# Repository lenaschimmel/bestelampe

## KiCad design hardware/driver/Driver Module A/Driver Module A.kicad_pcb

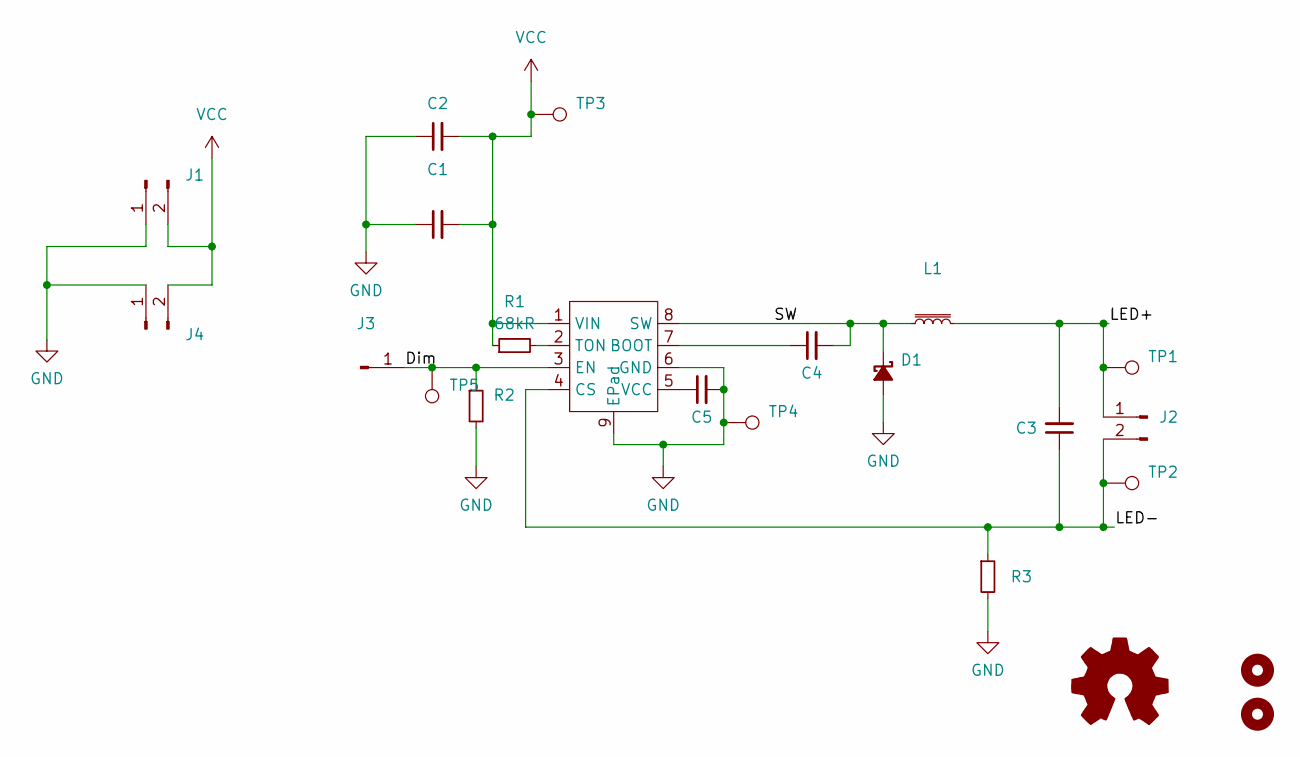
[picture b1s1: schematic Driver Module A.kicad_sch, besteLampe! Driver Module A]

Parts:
C1, C2, C4, C5: C_Small; C_1206_3216Metric
C3: 2.2uF; C_1206_3216Metric
D1: D_Schottky_Small_Filled; D_CMS04_M_FLAT
H1, H2: MountingHole; MountingHole_3.2mm_M3
J1, J2, J4: Conn_01x02_Pin; PinHeader_1x02_P2.54mm_Vertical
J3: Conn_01x01_Pin; PinHeader_1x01_P2.54mm_Vertical
L1: 10uH; L_Sumida_CDRH127
R1: 68kR; R_0805_2012Metric
R2: 10kR; R_0805_2012Metric
R3: R_Small; R_1206_3216Metric
TP1, TP2, TP3, TP4, TP5: TestPoint; TestPoint_THTPad_D1.5mm_Drill0.7mm
U1: SOIC-8-1EP_3.9x4.9mm_P1.27mm_EP2.41x3.3mm

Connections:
/Dim: J3.1, R2.1, TP5.1, U1.3 (EN)
/LED+: C3.2, J2.1, L1.2, TP1.1
/LED-: C3.1, J2.2, R3.1, TP2.1, U1.4 (CS)
/SW: C4.2, D1.1 (K), L1.1, U1.8 (SW)
GND: C1.1, C2.1, C5.2, D1.2 (A), J1.1, J4.1, R2.2, R3.2, TP4.1, U1.6 (GND), U1.9 (EPad)
unnamed: C4.1, U1.7 (BOOT)
unnamed: R1.2, U1.2 (TON)
unnamed: C5.1, U1.5 (VCC)
VCC: C1.2, C2.2, J1.2, J4.2, R1.1, TP3.1, U1.1 (VIN)

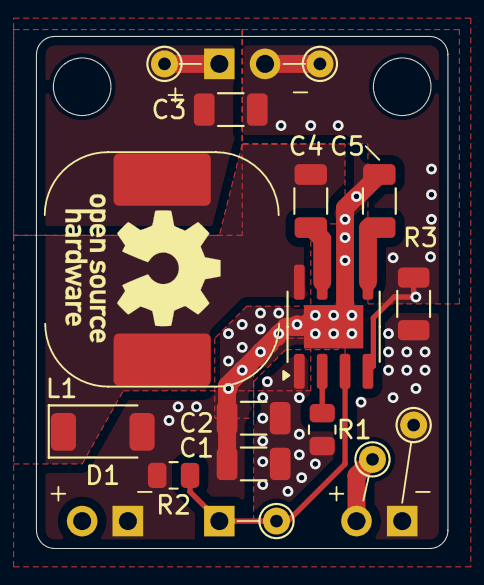
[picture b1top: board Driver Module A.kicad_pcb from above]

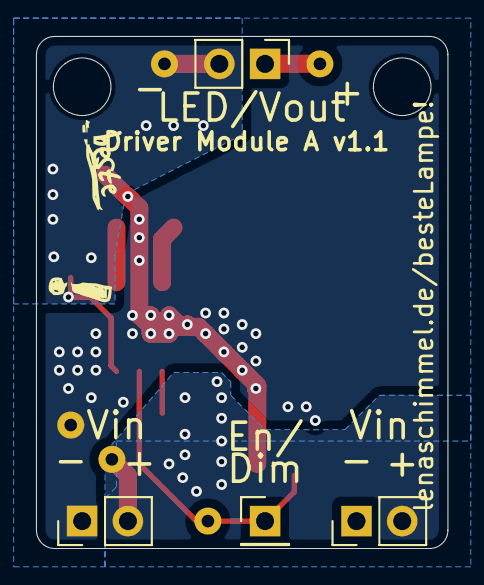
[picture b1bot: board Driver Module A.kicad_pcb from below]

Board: 2 copper layers, 22.9 x 28.4 mm, 22 parts (4 on the bottom side), 9 nets.

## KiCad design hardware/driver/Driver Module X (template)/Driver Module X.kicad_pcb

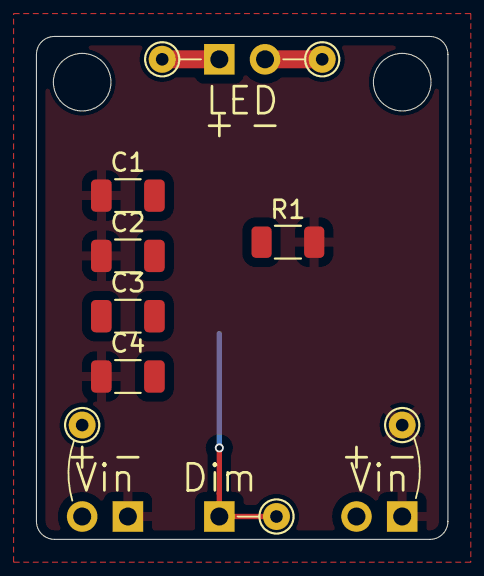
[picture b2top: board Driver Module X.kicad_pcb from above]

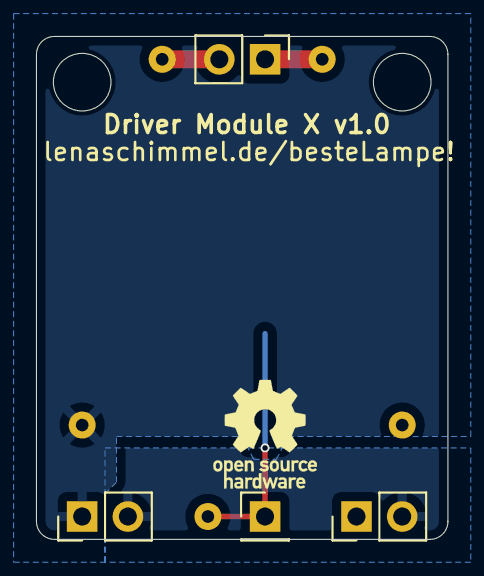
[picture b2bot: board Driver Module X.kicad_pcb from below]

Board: 2 copper layers, 22.9 x 27.9 mm, 16 parts (4 on the bottom side), 5 nets.

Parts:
C1, C2, C3, C4: C_Small; C_1206_3216Metric
H1, H2: MountingHole; MountingHole_3.2mm_M3
J1, J2, J4: Conn_01x02_Pin; PinHeader_1x02_P2.54mm_Vertical
J3: Conn_01x01_Pin; PinHeader_1x01_P2.54mm_Vertical
R1: R_Small; R_1206_3216Metric
TP1, TP2, TP3, TP4, TP5: TestPoint; TestPoint_THTPad_D1.5mm_Drill0.7mm

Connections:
/Dim: J3.1, TP5.1
/LED+: C4.2, J2.1, TP1.1
/LED-: J2.2, R1.1, TP2.1
GND: C1.1, C2.1, C4.1, J1.1, J4.1, R1.2, TP4.1
VCC: C1.2, C2.2, J1.2, J4.2, TP3.1

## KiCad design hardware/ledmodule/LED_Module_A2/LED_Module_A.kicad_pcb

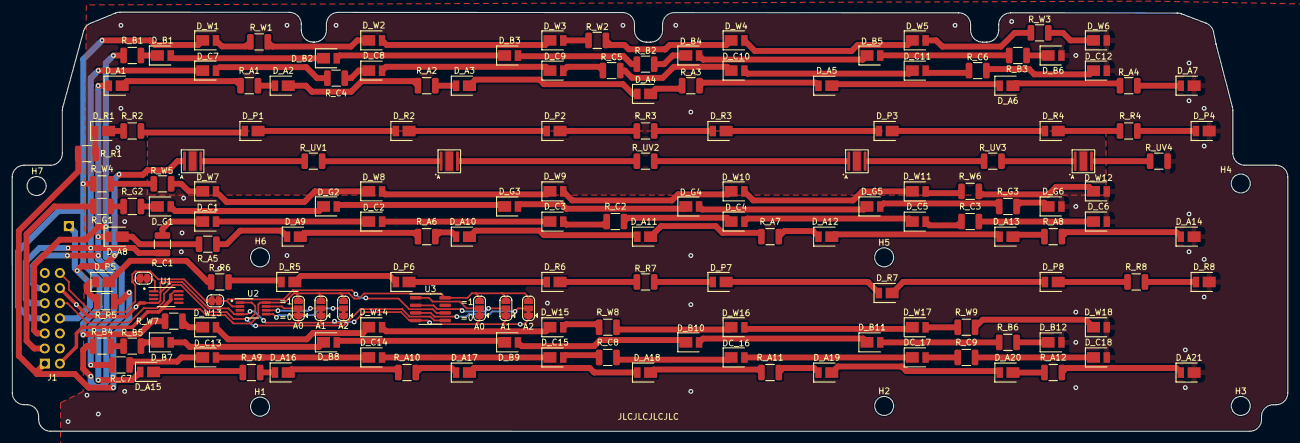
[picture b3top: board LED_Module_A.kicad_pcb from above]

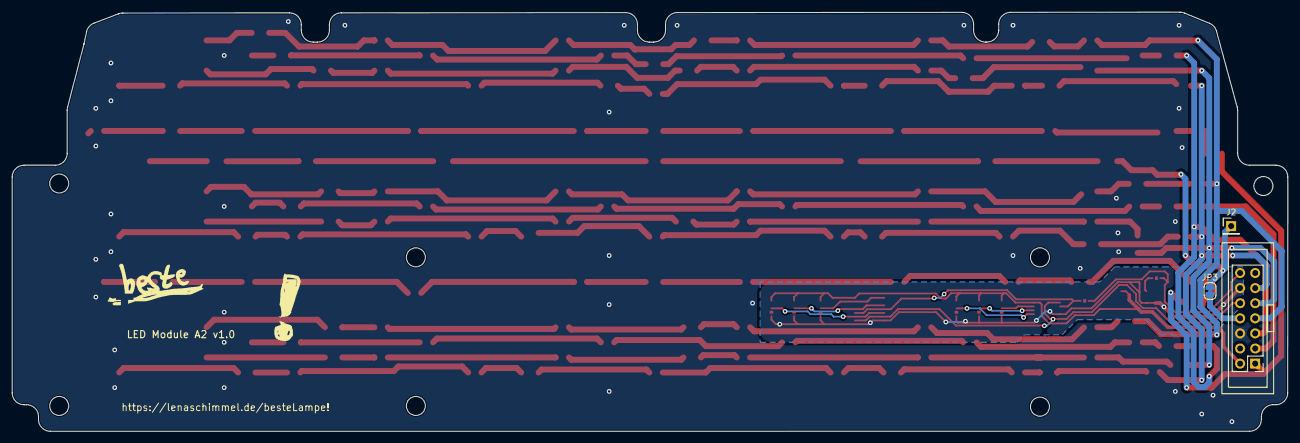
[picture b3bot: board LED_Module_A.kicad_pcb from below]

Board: 2 copper layers, 214.6 x 70.5 mm, 167 parts (3 on the bottom side), 153 nets.

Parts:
A0, A0b1, A1, A1b1, A2, A2b1: Jumper_3_Bridged12; SolderJumper-3_P1.3mm_Bridged12_RoundedPad1.0x1.5mm
DC_16, DC_17: Cold White; LED_2835_CREE_JSE28L3E5
D_A1, D_A2, D_A3, D_A4, D_A5, D_A6, D_A7, D_A8, D_A9, D_A10, D_A11, D_A12, D_A13, D_A14, D_A15, D_A16, D_A17, D_A18, D_A19, D_A20, D_A21: Amber; LED_2835_CREE_JSE28L3E5_Big_Anode
D_B1, D_B2, D_B3, D_B4, D_B5, D_B6, D_B7, D_B8, D_B9, D_B10, D_B11, D_B12: Royal Blue; LED_2835_CREE_JSE28L3E5
D_C1, D_C2, D_C3, D_C4, D_C5, D_C6, D_C7, D_C8, D_C9, D_C10, D_C11, D_C12, D_C13, D_C14, D_C15, D_C18: Cold White; LED_2835_CREE_JSE28L3E5
D_G1, D_G2, D_G3, D_G4, D_G5, D_G6: Green; LED_2835_CREE_JSE28L3E5
D_P1, D_P2, D_P3, D_P4, D_P5, D_P6, D_P7, D_P8: Photo Red; LED_2835_CREE_JSE28L3E5_Big_Anode
D_R1, D_R2, D_R3, D_R4, D_R5, D_R6, D_R7, D_R8: Red; LED_2835_CREE_JSE28L3E5_Big_Anode
D_UV1, D_UV2, D_UV3, D_UV4: Ultra Violet; Luminous Devices A130 Package
D_W1, D_W2, D_W3, D_W4, D_W5, D_W6, D_W7, D_W8, D_W9, D_W10, D_W11, D_W12, D_W13, D_W14, D_W15, D_W16, D_W17, D_W18: Warm White; LED_2835_CREE_JSE28L3E5
H1, H2, H3, H4, H5, H6, H7: MountingHole; MountingHole_3.2mm_M3
J1: Connector Header Surface Mount, Right Angle 14 po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; PinHeader_2x07_P2.54mm_Vertical_Boxed
J2: Conn_01x01; PinHeader_1x01_P2.54mm_Vertical
JP1, JP2, JP3: Jumper_2_Bridged; SolderJumper-2_P1.3mm_Bridged_RoundedPad1.0x1.5mm
R_A1, R_A5, R_A9: 2.2 Ohm, 0.33W, 5%, 1210 package; R_1210_3225Metric
R_A2, R_A3, R_A4, R_A6, R_A7, R_A8, R_A10, R_A11, R_A12: 18 Ohm, 0.5W, 1%, 1210 package; R_1210_3225Metric
R_B1, R_B2, R_B3, R_B4, R_B5, R_B6: 15 Ohm, 0.5W, 1%, 1210 package; R_1210_3225Metric
R_C1, R_C2, R_C3, R_C4, R_C5, R_C6, R_C7, R_C8, R_C9: 18 Ohm, 0.5W, 1%, 1210 package; R_1210_3225Metric
R_G1, R_G2, R_G3: 18 Ohm, 0.5W, 1%, 1210 package; R_1210_3225Metric
R_R1, R_R5: 4.7 Ohm, 0.33W, 5%, 1210 package; R_1210_3225Metric
R_R2, R_R3, R_R4, R_R6, R_R7, R_R8: 15 Ohm, 0.5W, 1%, 1210 package; R_1210_3225Metric
R_UV1, R_UV2, R_UV3, R_UV4: 4.7 Ohm, 0.33W, 5%, 1210 package; R_1210_3225Metric
R_W1, R_W2, R_W3, R_W4, R_W5, R_W6, R_W7, R_W8, R_W9: 18 Ohm, 0.5W, 1%, 1210 package; R_1210_3225Metric
U1: DS18B20U+; MSOP-8_3x3mm_P0.65mm
U2: TMP1075DGK; VSSOP-8_3.0x3.0mm_P0.65mm
U3: 24AA02-OT; SOIC-8_3.9x4.9mm_P1.27mm

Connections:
+3V3: A0.3 (B), A0b1.3 (B), A1.3 (B), A1b1.3 (B), A2.3 (B), A2b1.3 (B), J1.2, U1.8 (V_{DD}), U2.8 (V+), U3.8 (V_{CC})
+24V: D_A7.1 (A), D_A14.1 (A), D_A21.1 (A), D_B6.2 (A), D_B12.2 (A), D_C6.2 (A), D_C12.2 (A), D_C18.2 (A), D_G6.2 (A), D_P4.1 (A), D_R8.1 (A), D_W6.2 (A), D_W12.2 (A), D_W18.2 (A), J1.6, R_UV4.2
/LED_A: D_A1.2 (K), D_A8.2 (K), D_A15.2 (K), J1.11
/LED_B: J1.5, R_B1.1, R_B4.1
/LED_CW: D_C7.1 (K), J1.9, R_C1.1, R_C7.1
/LED_G: J1.3, R_G1.1
/LED_R: J1.1, R_R1.2, R_R5.1
/LED_UV: J1.8, JP3.2 (B)
/LED_WW: D_W1.1 (K), J1.7, R_W4.1, R_W7.1
/SDA: J1.10, U2.1 (SDA), U3.5 (SDA)
/TEMP_SCL: J1.14, JP1.1 (A), JP2.2 (B)
/Thermal: D_UV1.3 (Thermal), D_UV2.3 (Thermal), D_UV3.3 (Thermal), D_UV4.3 (Thermal)
GND: A0.1 (A), A0b1.1 (A), A1.1 (A), A1b1.1 (A), A2.1 (A), A2b1.1 (A), J1.12, U1.4 (GND), U2.4 (GND), U3.4 (V_{SS})
unnamed: A0.2 (C), U2.7 (A0)
unnamed: A0b1.2 (C), U3.1 (A0)
unnamed: A1.2 (C), U2.6 (A1)
unnamed: A1b1.2 (C), U3.2 (A1)
unnamed: A2.2 (C), U2.5 (A2)
unnamed: A2b1.2 (C), U3.3 (A2)
unnamed: DC_16.2 (A), DC_17.1 (K)
unnamed: DC_16.1 (K), R_C8.2
unnamed: DC_17.2 (A), R_C9.1
unnamed: D_A1.1 (A), R_A1.1
unnamed: D_A2.1 (A), R_A2.1
unnamed: D_A2.2 (K), R_A1.2
unnamed: D_A3.1 (A), D_A4.2 (K)
unnamed: D_A3.2 (K), R_A2.2
unnamed: D_A4.1 (A), R_A3.1
unnamed: D_A5.1 (A), D_A6.2 (K)
unnamed: D_A5.2 (K), R_A3.2
unnamed: D_A6.1 (A), R_A4.1
unnamed: D_A7.2 (K), R_A4.2
unnamed: D_A8.1 (A), R_A5.1
unnamed: D_A9.1 (A), R_A6.1
unnamed: D_A9.2 (K), R_A5.2
unnamed: D_A10.1 (A), D_A11.2 (K)
unnamed: D_A10.2 (K), R_A6.2
unnamed: D_A11.1 (A), R_A7.1
unnamed: D_A12.1 (A), D_A13.2 (K)
unnamed: D_A12.2 (K), R_A7.2
unnamed: D_A13.1 (A), R_A8.1
unnamed: D_A14.2 (K), R_A8.2
unnamed: D_A15.1 (A), R_A9.1
unnamed: D_A16.1 (A), R_A10.1
unnamed: D_A16.2 (K), R_A9.2
unnamed: D_A17.1 (A), D_A18.2 (K)
unnamed: D_A17.2 (K), R_A10.2
unnamed: D_A18.1 (A), R_A11.1
unnamed: D_A19.1 (A), D_A20.2 (K)
unnamed: D_A19.2 (K), R_A11.2
unnamed: D_A20.1 (A), R_A12.1
unnamed: D_A21.2 (K), R_A12.2
unnamed: D_B1.2 (A), D_B2.1 (K)
unnamed: D_B1.1 (K), R_B1.2
unnamed: D_B2.2 (A), D_B3.1 (K)
unnamed: D_B3.2 (A), R_B2.1
unnamed: D_B4.2 (A), D_B5.1 (K)
unnamed: D_B4.1 (K), R_B2.2
unnamed: D_B5.2 (A), R_B3.1
unnamed: D_B6.1 (K), R_B3.2
unnamed: D_B7.2 (A), D_B8.1 (K)
unnamed: D_B7.1 (K), R_B5.2
unnamed: D_B8.2 (A), D_B9.1 (K)
unnamed: D_B10.2 (A), D_B11.1 (K)
unnamed: D_B9.2 (A), D_B10.1 (K)
unnamed: D_B11.2 (A), R_B6.1
unnamed: D_B12.1 (K), R_B6.2
unnamed: D_C1.2 (A), D_C2.1 (K)
unnamed: D_C1.1 (K), R_C1.2
unnamed: D_C2.2 (A), D_C3.1 (K)
unnamed: D_C3.2 (A), R_C2.1
unnamed: D_C4.2 (A), D_C5.1 (K)
unnamed: D_C4.1 (K), R_C2.2
unnamed: D_C5.2 (A), R_C3.1
unnamed: D_C6.1 (K), R_C3.2
unnamed: D_C7.2 (A), R_C4.1
unnamed: D_C8.2 (A), D_C9.1 (K)
unnamed: D_C8.1 (K), R_C4.2
unnamed: D_C9.2 (A), R_C5.1
unnamed: D_C10.2 (A), D_C11.1 (K)
unnamed: D_C10.1 (K), R_C5.2
unnamed: D_C11.2 (A), R_C6.1
unnamed: D_C12.1 (K), R_C6.2
unnamed: D_C13.2 (A), D_C14.1 (K)
unnamed: D_C13.1 (K), R_C7.2
unnamed: D_C14.2 (A), D_C15.1 (K)
unnamed: D_C15.2 (A), R_C8.1
unnamed: D_C18.1 (K), R_C9.2
unnamed: D_G1.2 (A), D_G2.1 (K)
unnamed: D_G1.1 (K), R_G2.2
unnamed: D_G2.2 (A), D_G3.1 (K)
unnamed: D_G3.2 (A), D_G4.1 (K)
unnamed: D_G4.2 (A), D_G5.1 (K)
unnamed: D_G5.2 (A), R_G3.1
unnamed: D_G6.1 (K), R_G3.2
unnamed: D_P1.1 (A), D_R2.2 (K)
unnamed: D_P1.2 (K), R_R2.2
unnamed: D_P2.1 (A), R_R3.1
unnamed: D_P2.2 (K), D_R2.1 (A)
unnamed: D_P3.1 (A), D_R4.2 (K)
unnamed: D_P3.2 (K), D_R3.1 (A)
unnamed: D_P4.2 (K), R_R4.2
unnamed: D_P5.1 (A), R_R6.1
unnamed: D_P5.2 (K), R_R5.2
unnamed: D_P6.1 (A), D_R6.2 (K)
unnamed: D_P6.2 (K), D_R5.1 (A)
unnamed: D_P7.1 (A), D_R7.2 (K)
unnamed: D_P7.2 (K), R_R7.2
unnamed: D_P8.1 (A), R_R8.1
unnamed: D_P8.2 (K), D_R7.1 (A)
unnamed: D_R1.1 (A), R_R2.1
unnamed: D_R1.2 (K), R_R1.1
unnamed: D_R3.2 (K), R_R3.2
unnamed: D_R4.1 (A), R_R4.1
unnamed: D_R5.2 (K), R_R6.2
unnamed: D_R6.1 (A), R_R7.1
unnamed: D_R8.2 (K), R_R8.2
unnamed: D_UV1.2 (A), R_UV1.1
unnamed: D_UV1.1 (K), J2.1, JP3.1 (A)
unnamed: D_UV2.2 (A), R_UV2.1
unnamed: D_UV2.1 (K), R_UV1.2
unnamed: D_UV3.2 (A), R_UV3.1
unnamed: D_UV3.1 (K), R_UV2.2
unnamed: D_UV4.2 (A), R_UV4.1
unnamed: D_UV4.1 (K), R_UV3.2
unnamed: D_W1.2 (A), R_W1.1
unnamed: D_W2.2 (A), D_W3.1 (K)
unnamed: D_W2.1 (K), R_W1.2
unnamed: D_W3.2 (A), R_W2.1
unnamed: D_W4.2 (A), D_W5.1 (K)
unnamed: D_W4.1 (K), R_W2.2
unnamed: D_W5.2 (A), R_W3.1
unnamed: D_W6.1 (K), R_W3.2
unnamed: D_W7.2 (A), D_W8.1 (K)
unnamed: D_W7.1 (K), R_W5.2
unnamed: D_W8.2 (A), D_W9.1 (K)
unnamed: D_W10.2 (A), D_W11.1 (K)
unnamed: D_W9.2 (A), D_W10.1 (K)
unnamed: D_W11.2 (A), R_W6.1
unnamed: D_W12.1 (K), R_W6.2
unnamed: D_W13.2 (A), D_W14.1 (K)
unnamed: D_W13.1 (K), R_W7.2
unnamed: D_W14.2 (A), D_W15.1 (K)
unnamed: D_W15.2 (A), R_W8.1
unnamed: D_W16.2 (A), D_W17.1 (K)
unnamed: D_W16.1 (K), R_W8.2
unnamed: D_W17.2 (A), R_W9.1
unnamed: D_W18.1 (K), R_W9.2
unnamed: JP1.2 (B), U2.2 (SCL), U3.6 (SCL)
unnamed: JP2.1 (A), U1.1 (DQ)
unnamed: R_B4.2, R_B5.1
unnamed: R_G1.2, R_G2.1
unnamed: R_W4.2, R_W5.1

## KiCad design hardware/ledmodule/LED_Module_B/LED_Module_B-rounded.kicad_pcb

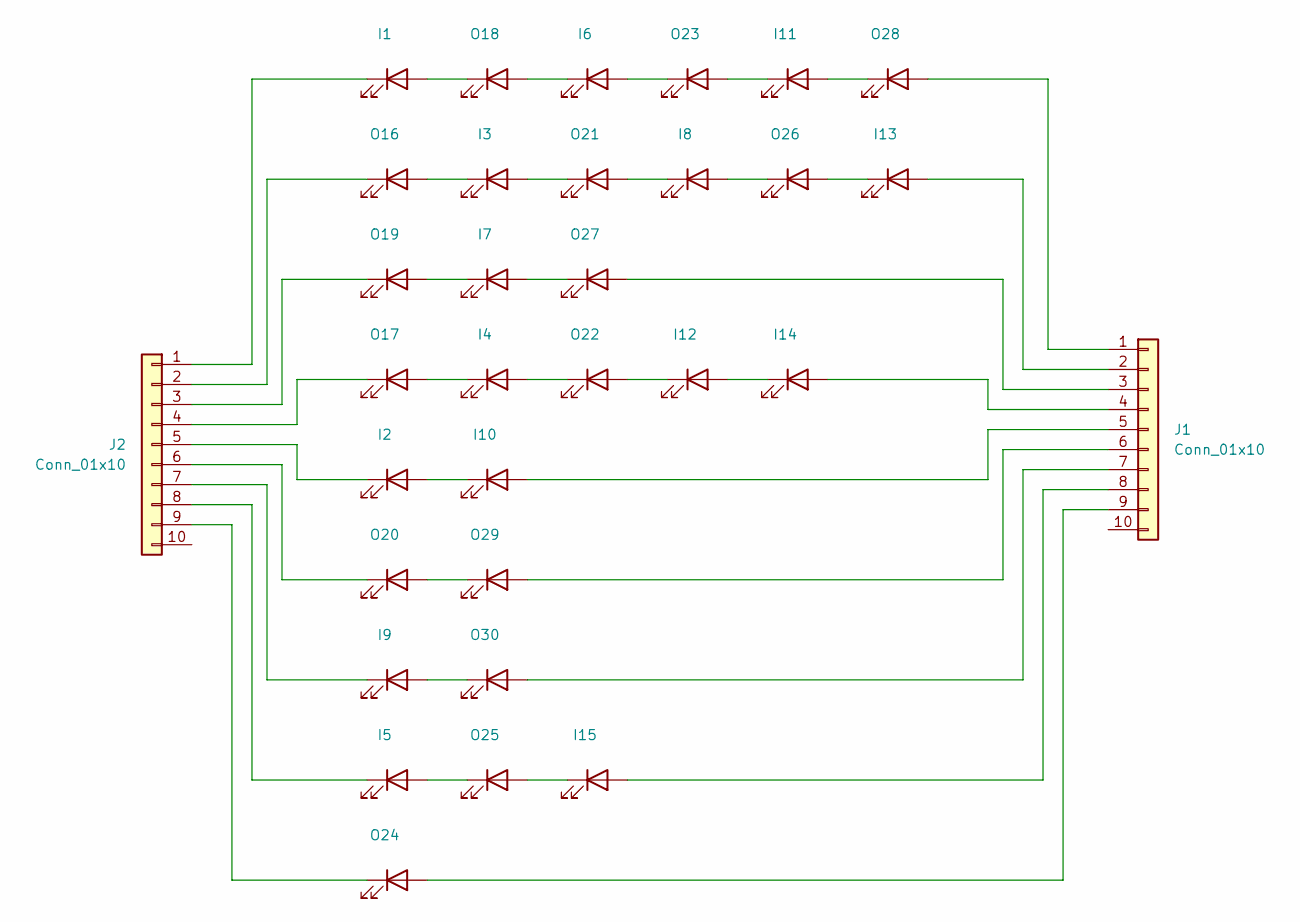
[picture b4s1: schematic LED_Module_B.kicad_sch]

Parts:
I1, I6, I11: Warm white 3000K; LED_2835_CREE_JSE28L3E5_1
I2, I7, I10: LED_2835_CREE_JSE28L3E5_Big_Anode
I3, I8, I13: Cold white 5700K; LED_2835_CREE_JSE28L3E5_1
I4, I5, I9, I12, I14, I15: LED_2835_CREE_JSE28L3E5_1
J1, J2: Conn_01x10; PinHeader_1x10_P2.54mm_Vertical
O16, O21, O26: Cold white 5700K; LED_2835_CREE_JSE28L3E5_1
O17, O22, O25, O30: LED_2835_CREE_JSE28L3E5_1
O18, O23, O28: Warm white 3000K; LED_2835_CREE_JSE28L3E5_1
O19: I12; LED_2835_CREE_JSE28L3E5_Big_Anode
O20, O27, O29: LED_2835_CREE_JSE28L3E5_Big_Anode
O24: Luminous Devices A130 Package

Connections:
unnamed: I1.2 (A), O18.1 (K)
unnamed: I1.1 (K), J2.1
unnamed: I2.1 (K), J2.5
unnamed: I3.2 (A), O21.1 (K)
unnamed: I3.1 (K), O16.2 (A)
unnamed: I4.2 (A), O22.1 (K)
unnamed: I4.1 (K), O17.2 (A)
unnamed: I5.2 (A), O25.1 (K)
unnamed: I5.1 (K), J2.8
unnamed: I6.2 (A), O23.1 (K)
unnamed: I6.1 (K), O18.2 (A)
unnamed: I7.2 (A), O27.1 (K)
unnamed: I7.1 (K), O19.2 (A)
unnamed: I8.2 (A), O26.1 (K)
unnamed: I8.1 (K), O21.2 (A)
unnamed: I9.2 (A), O30.1 (K)
unnamed: I9.1 (K), J2.7
unnamed: I10.2 (A), J1.5
unnamed: I2.2 (A), I10.1 (K)
unnamed: I11.2 (A), O28.1 (K)
unnamed: I11.1 (K), O23.2 (A)
unnamed: I12.2 (A), I14.1 (K)
unnamed: I12.1 (K), O22.2 (A)
unnamed: I13.2 (A), J1.2
unnamed: I13.1 (K), O26.2 (A)
unnamed: I14.2 (A), J1.4
unnamed: I15.2 (A), J1.8
unnamed: I15.1 (K), O25.2 (A)
unnamed: J1.1, O28.2 (A)
unnamed: J1.3, O27.2 (A)
unnamed: J1.6, O29.2 (A)
unnamed: J1.7, O30.2 (A)
unnamed: J1.9, O24.2 (A)
unnamed: J2.2, O16.1 (K)
unnamed: J2.3, O19.1 (K)
unnamed: J2.4, O17.1 (K)
unnamed: J2.6, O20.1 (K)
unnamed: J2.9, O24.1 (K)
unnamed: O20.2 (A), O29.1 (K)

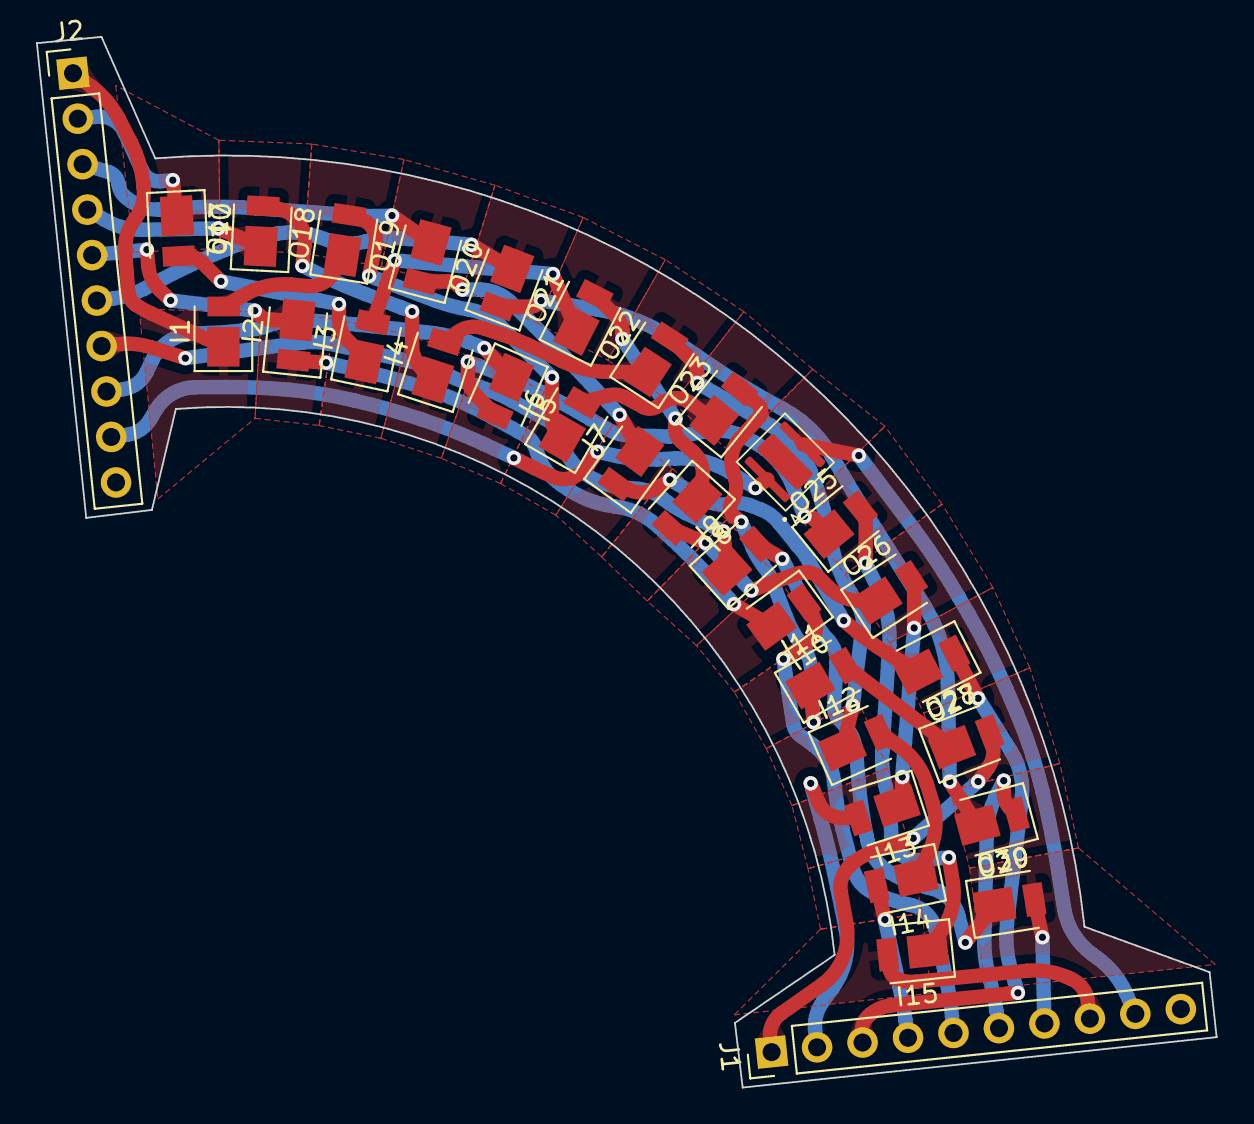
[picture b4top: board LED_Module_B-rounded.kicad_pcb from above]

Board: 2 copper layers, 65.5 x 58.4 mm, 32 parts (0 on the bottom side), 39 nets.

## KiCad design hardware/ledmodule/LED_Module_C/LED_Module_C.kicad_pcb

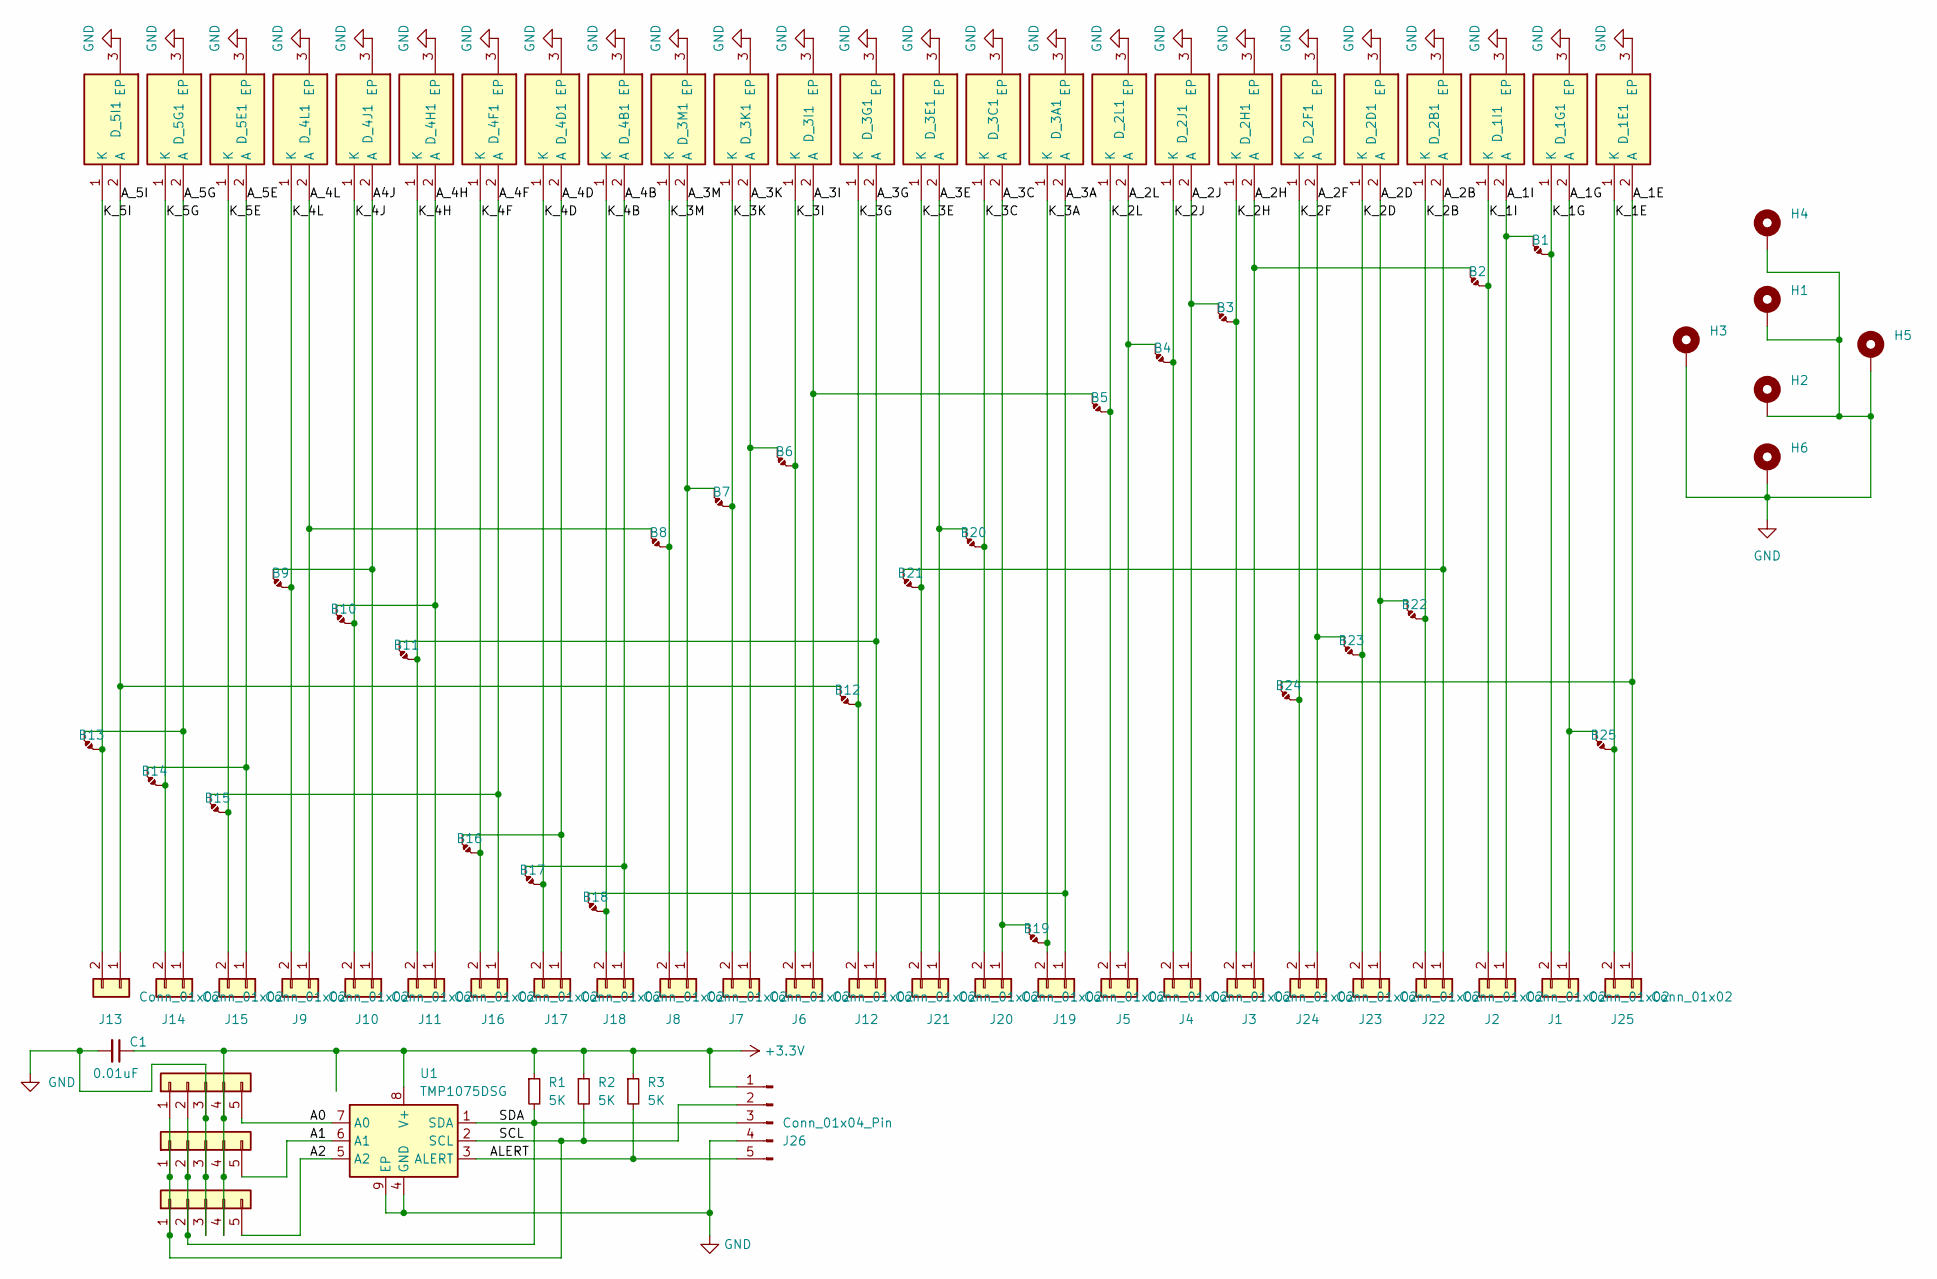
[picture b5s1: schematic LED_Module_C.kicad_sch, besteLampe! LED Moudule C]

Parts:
B1, B2, B3, B4, B5, B6, B7, B8, B9, B10, B11, B12, B13, B14, B15, B16, B17, B18, B19, B20, B21, B22, B23, B24, B25: SolderJumper-2_P1.3mm_Open_TrianglePad1.0x1.5mm
C1: 0.01uF; C_0402_1005Metric
D_1E1, D_1G1, D_1I1, D_2B1, D_2D1, D_2F1, D_2H1, D_2J1, D_2L1, D_3A1, D_3C1, D_3E1, D_3G1, D_3I1, D_3K1, D_3M1, D_4B1, D_4D1, D_4F1, D_4H1, D_4J1, D_4L1, D_5E1, D_5G1, D_5I1: XEGAVTH_clean; Manufacturer_Part_Number XEGAVT-H0-0000-000-000000K2001
H1, H2, H3, H4, H5, H6: MountingHole_Pad; MountingHole_3.2mm_M3_DIN965_Pad_TopBottom
J1, J2, J3, J4, J5, J6, J7, J8, J9, J10, J11, J12, J13, J14, J15, J16, J17, J18, J19, J20, J21, J22, J23, J24, J25: Conn_01x02; PinHeader_1x02_P2.54mm_Vertical
J26: Conn_01x04_Pin; PinHeader_1x05_P2.54mm_Horizontal
J27, J28, J29: Conn_01x05; Quadforce
R1, R2, R3: 5K; R_0603_1608Metric
U1: TMP1075DSG; WSON-8-1EP_2x2mm_P0.5mm_EP0.9x1.6mm_ThermalVias

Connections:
+3.3V: C1.1, J26.1, J27.4, J28.4, J29.4, R1.1, R2.1, R3.1, U1.8 (V+)
/A0: J27.5, U1.7 (A0)
/A1: J28.5, U1.6 (A1)
/A2: J29.5, U1.5 (A2)
/A4J: B9.1, D_4J1.2 (A), J10.1
/ALERT: J26.5, R3.2, U1.3 (ALERT)
/A_1E: B24.1, D_1E1.2 (A), J25.1
/A_1G: B25.1, D_1G1.2 (A), J1.1
/A_1I: B1.1, D_1I1.2 (A), J2.1
/A_2B: B21.1, D_2B1.2 (A), J22.1
/A_2D: B22.1, D_2D1.2 (A), J23.1
/A_2F: B23.1, D_2F1.2 (A), J24.1
/A_2H: B2.1, D_2H1.2 (A), J3.1
/A_2J: B3.1, D_2J1.2 (A), J4.1
/A_2L: B4.1, D_2L1.2 (A), J5.1
/A_3A: B18.1, D_3A1.2 (A), J19.1
/A_3C: B19.1, D_3C1.2 (A), J20.1
/A_3E: B20.1, D_3E1.2 (A), J21.1
/A_3G: B11.1, D_3G1.2 (A), J12.1
/A_3I: B5.1, D_3I1.2 (A), J6.1
/A_3K: B6.1, D_3K1.2 (A), J7.1
/A_3M: B7.1, D_3M1.2 (A), J8.1
/A_4B: B17.1, D_4B1.2 (A), J18.1
/A_4D: B16.1, D_4D1.2 (A), J17.1
/A_4F: B15.1, D_4F1.2 (A), J16.1
/A_4H: B10.1, D_4H1.2 (A), J11.1
/A_4L: B8.1, D_4L1.2 (A), J9.1
/A_5E: B14.1, D_5E1.2 (A), J15.1
/A_5G: B13.1, D_5G1.2 (A), J14.1
/A_5I: B12.1, D_5I1.2 (A), J13.1
/K_1E: B25.2, D_1E1.1 (K), J25.2
/K_1G: B1.2, D_1G1.1 (K), J1.2
/K_1I: B2.2, D_1I1.1 (K), J2.2
/K_2B: B22.2, D_2B1.1 (K), J22.2
/K_2D: B23.2, D_2D1.1 (K), J23.2
/K_2F: B24.2, D_2F1.1 (K), J24.2
/K_2H: B3.2, D_2H1.1 (K), J3.2
/K_2J: B4.2, D_2J1.1 (K), J4.2
/K_2L: B5.2, D_2L1.1 (K), J5.2
/K_3A: B19.2, D_3A1.1 (K), J19.2
/K_3C: B20.2, D_3C1.1 (K), J20.2
/K_3E: B21.2, D_3E1.1 (K), J21.2
/K_3G: B12.2, D_3G1.1 (K), J12.2
/K_3I: B6.2, D_3I1.1 (K), J6.2
/K_3K: B7.2, D_3K1.1 (K), J7.2
/K_3M: B8.2, D_3M1.1 (K), J8.2
/K_4B: B18.2, D_4B1.1 (K), J18.2
/K_4D: B17.2, D_4D1.1 (K), J17.2
/K_4F: B16.2, D_4F1.1 (K), J16.2
/K_4H: B11.2, D_4H1.1 (K), J11.2
/K_4J: B10.2, D_4J1.1 (K), J10.2
/K_4L: B9.2, D_4L1.1 (K), J9.2
/K_5E: B15.2, D_5E1.1 (K), J15.2
/K_5G: B14.2, D_5G1.1 (K), J14.2
/K_5I: B13.2, D_5I1.1 (K), J13.2
/SCL: J26.2, J27.1, J28.1, J29.1, R2.2, U1.2 (SCL)
/SDA: J26.3, J27.2, J28.2, J29.2, R1.2, U1.1 (SDA)
GND: C1.2, D_1E1.3 (EP), D_1G1.3 (EP), D_1I1.3 (EP), D_2B1.3 (EP), D_2D1.3 (EP), D_2F1.3 (EP), D_2H1.3 (EP), D_2J1.3 (EP), D_2L1.3 (EP), D_3A1.3 (EP), D_3C1.3 (EP), D_3E1.3 (EP), D_3G1.3 (EP), D_3I1.3 (EP), D_3K1.3 (EP), D_3M1.3 (EP), D_4B1.3 (EP), D_4D1.3 (EP), D_4F1.3 (EP), D_4H1.3 (EP), D_4J1.3 (EP), D_4L1.3 (EP), D_5E1.3 (EP), D_5G1.3 (EP), D_5I1.3 (EP), H1.1, H2.1, H3.1, H4.1, H5.1, H6.1, J26.4, J27.3, J28.3, J29.3, U1.4 (GND), U1.9 (EP)

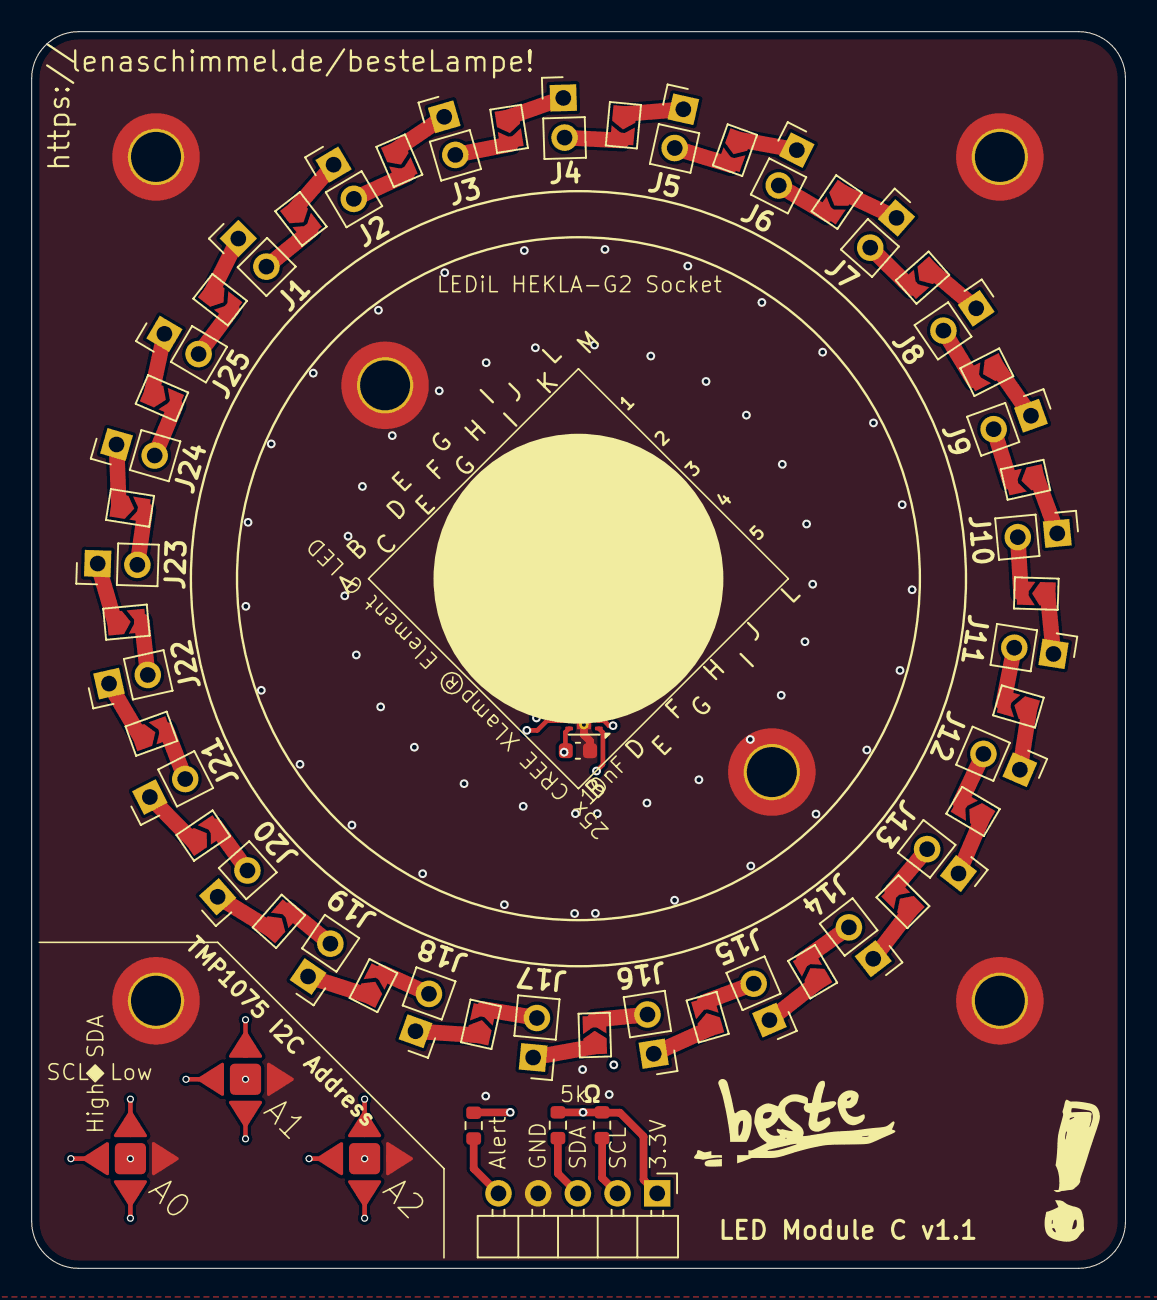
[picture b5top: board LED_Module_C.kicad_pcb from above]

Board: 4 copper layers, 70.0 x 79.1 mm, 90 parts (0 on the bottom side), 58 nets.

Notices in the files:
hardware/driver/Driver Module A/Driver Module A.kicad_pcb:
This source describes Open Hardware and is licensed under the CERN-OHL-S v2.
Copyright 2024 Lena Schimmel
